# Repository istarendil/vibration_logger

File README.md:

# vibration_logger
The main idea of this project is to build a device capable of measuring vibrations in structures such as buildings and transmitting the information obtained to a database that can be accessed remotely through the internet. The objective of having a remote monitoring system is to collect useful data on the state of the buildings for its later analysis.

This project was commissioned by the Department of Structural Analysis of the Faculty of Engineering of the Autonomous University of the State of Mexico to the System Dynamics and Control Laboratory. 

# Tools and materials
- esp8266
- dsPic30f3014
- RTC DS1302

# Software
|name| version|
|----|--------|
|MPLAB X| 10 |
|C16 compiler|1.25|
|Matlab| 2016|

# Directories and files
- The firmware/logger directory contains the source code written for the C16 compiler in MPLAB X.
- The firmware/esp8266 folder contains the different versions of the esp8266 firmware.
- The firmware/configuration_files folder contains the necessary files for the operation of the logger and for the connection to the Wi-fi network, as well as a file that shows how the data is stored.
- The pcb folder contains the PCB design files.
- The Excel document at te test folder contains a test performed on the prototype, where data was acquired and the results were graphed.

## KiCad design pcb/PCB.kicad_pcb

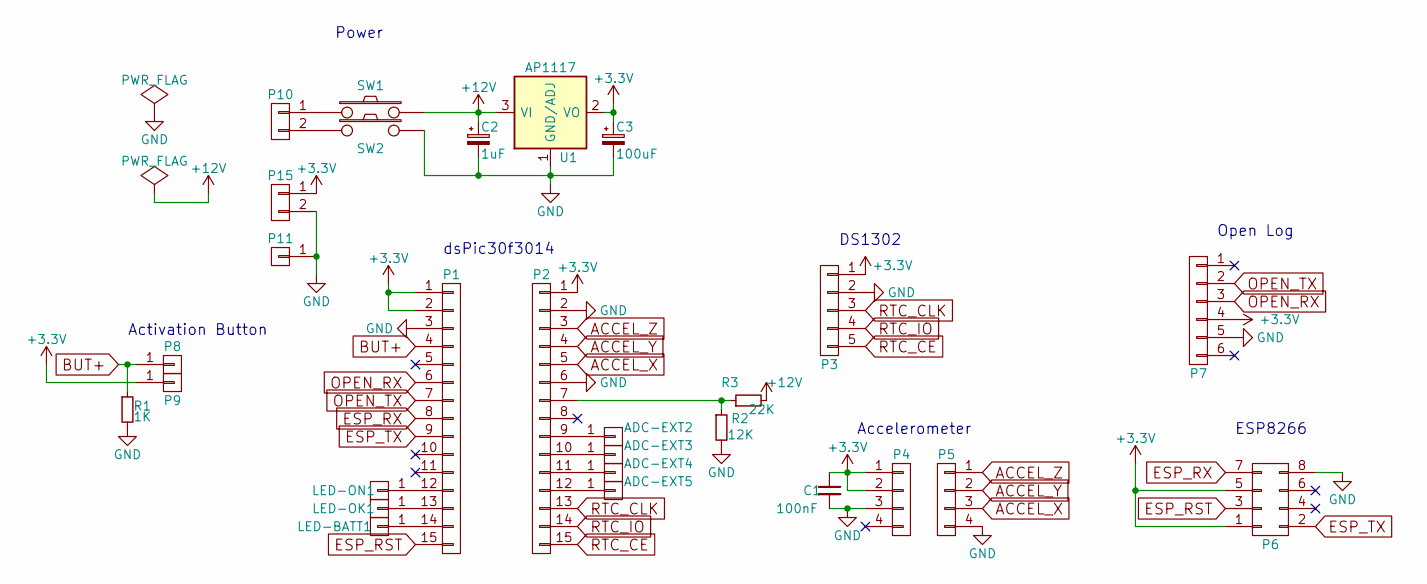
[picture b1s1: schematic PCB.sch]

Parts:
ADC-EXT2, ADC-EXT3, ADC-EXT4, ADC-EXT5: CONN_01X01; Socket_Strip_Straight_1x01
C1: 100nF; C_1206_HandSoldering
C2: 1uF; c_tant_A
C3: 100uF; c_tant_C
LED-BATT1: CONN_01X01; Socket_Strip_Straight_1x01
LED-OK1: CONN_01X01; Socket_Strip_Straight_1x01
LED-ON1: CONN_01X01; Socket_Strip_Straight_1x01
P1, P2: CONN_01X15; Socket_Strip_Straight_1x15
P3: CONN_01X05; Socket_Strip_Straight_1x05
P4, P5: CONN_01X04; Socket_Strip_Straight_1x04
P6: CONN_02X04; Socket_Strip_Straight_2x04
P7: CONN_01X06; Socket_Strip_Straight_1x06
P8, P9, P11: CONN_01X01; Socket_Strip_Straight_1x01
P10, P15: CONN_01X02; Socket_Strip_Straight_1x02
R1: 1K; R_0805_HandSoldering
R2: 12K; R_0805_HandSoldering
R3: 22K; R_0805_HandSoldering
SW1, SW2: SW_PUSH; Socket_Strip_Straight_1x02
U1: AP1117; sot223

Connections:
+3V3: C1.1, C3.1, P1.1, P1.2, P2.1, P3.1, P4.1, P4.2, P6.1, P6.5, P7.4, P9.1, P15.1, U1.2 (VO)
+12V: C2.1, R3.2, SW1.2, U1.3 (VI)
ACCEL_X: P2.5, P5.3
ACCEL_Y: P2.4, P5.2
ACCEL_Z: P2.3, P5.1
BUT+: P1.4, P8.1, R1.1
ESP_RST: P1.15, P6.3
ESP_RX: P1.8, P6.7
ESP_TX: P1.9, P6.2
GND: C1.2, C2.2, C3.2, P1.3, P2.2, P2.6, P3.2, P4.3, P5.4, P6.8, P7.5, P11.1, P15.2, R1.2, R2.2, SW2.2, U1.1 (GND/ADJ)
unnamed: ADC-EXT2.1, P2.9
unnamed: ADC-EXT3.1, P2.10
unnamed: ADC-EXT4.1, P2.11
unnamed: ADC-EXT5.1, P2.12
unnamed: LED-BATT1.1, P1.14
unnamed: LED-OK1.1, P1.13
unnamed: LED-ON1.1, P1.12
unnamed: P2.7, R2.1, R3.1
unnamed: P10.1, SW1.1
unnamed: P10.2, SW2.1
OPEN_RX: P1.6, P7.3
OPEN_TX: P1.7, P7.2
RTC_CE: P2.15, P3.5
RTC_CLK: P2.13, P3.3
RTC_IO: P2.14, P3.4

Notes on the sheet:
dsPic30f3014
DS1302
Open Log
Accelerometer
ESP8266
Power
Activation Button

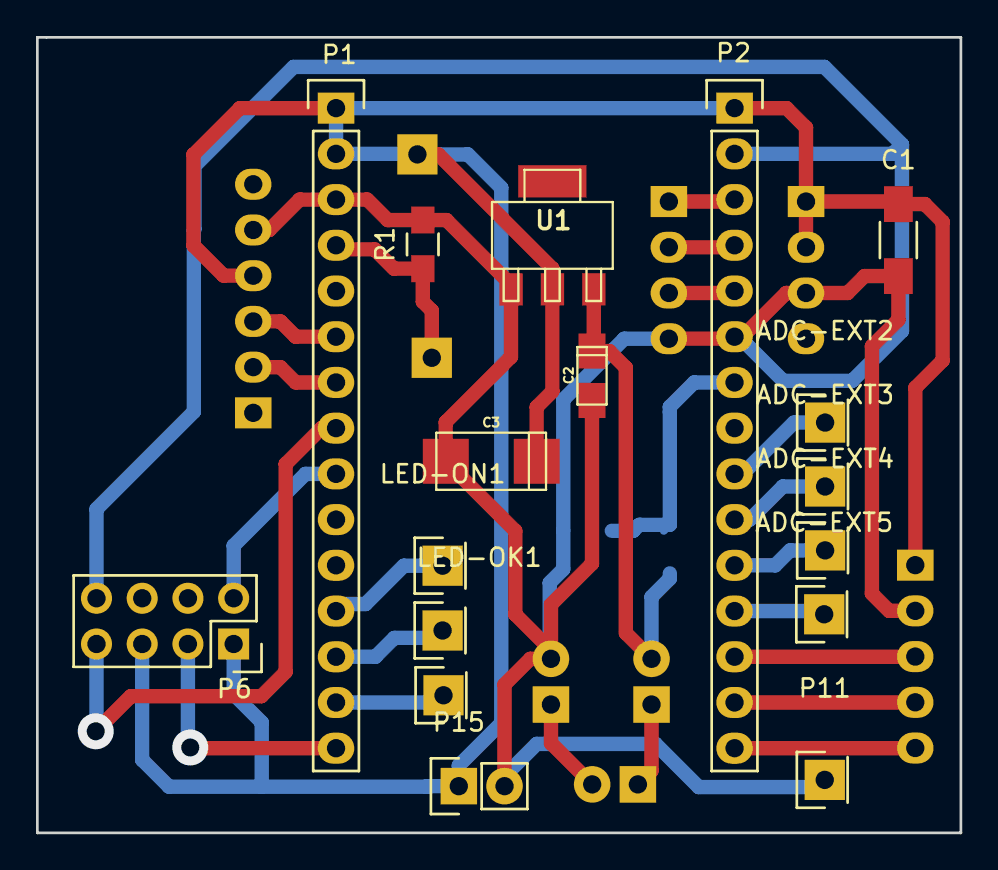
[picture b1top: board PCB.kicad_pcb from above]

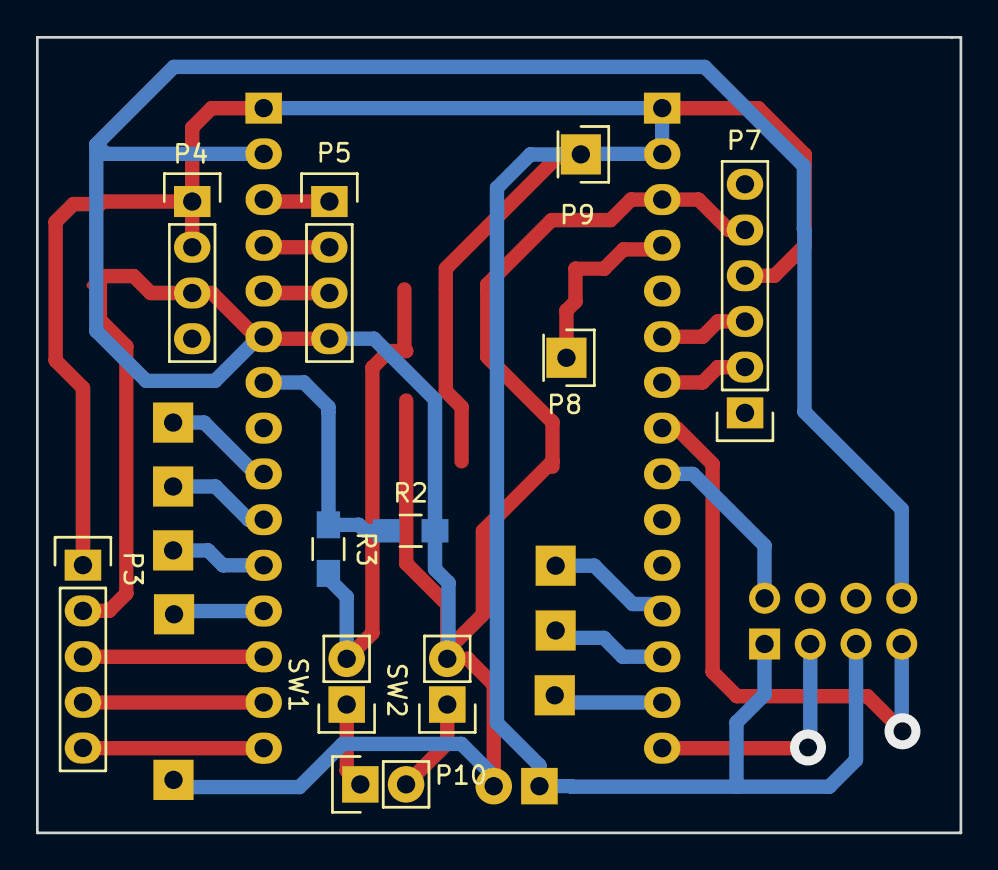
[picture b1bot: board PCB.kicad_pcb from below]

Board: 2 copper layers, 51.3 x 44.2 mm, 28 parts (11 on the bottom side), 25 nets.
